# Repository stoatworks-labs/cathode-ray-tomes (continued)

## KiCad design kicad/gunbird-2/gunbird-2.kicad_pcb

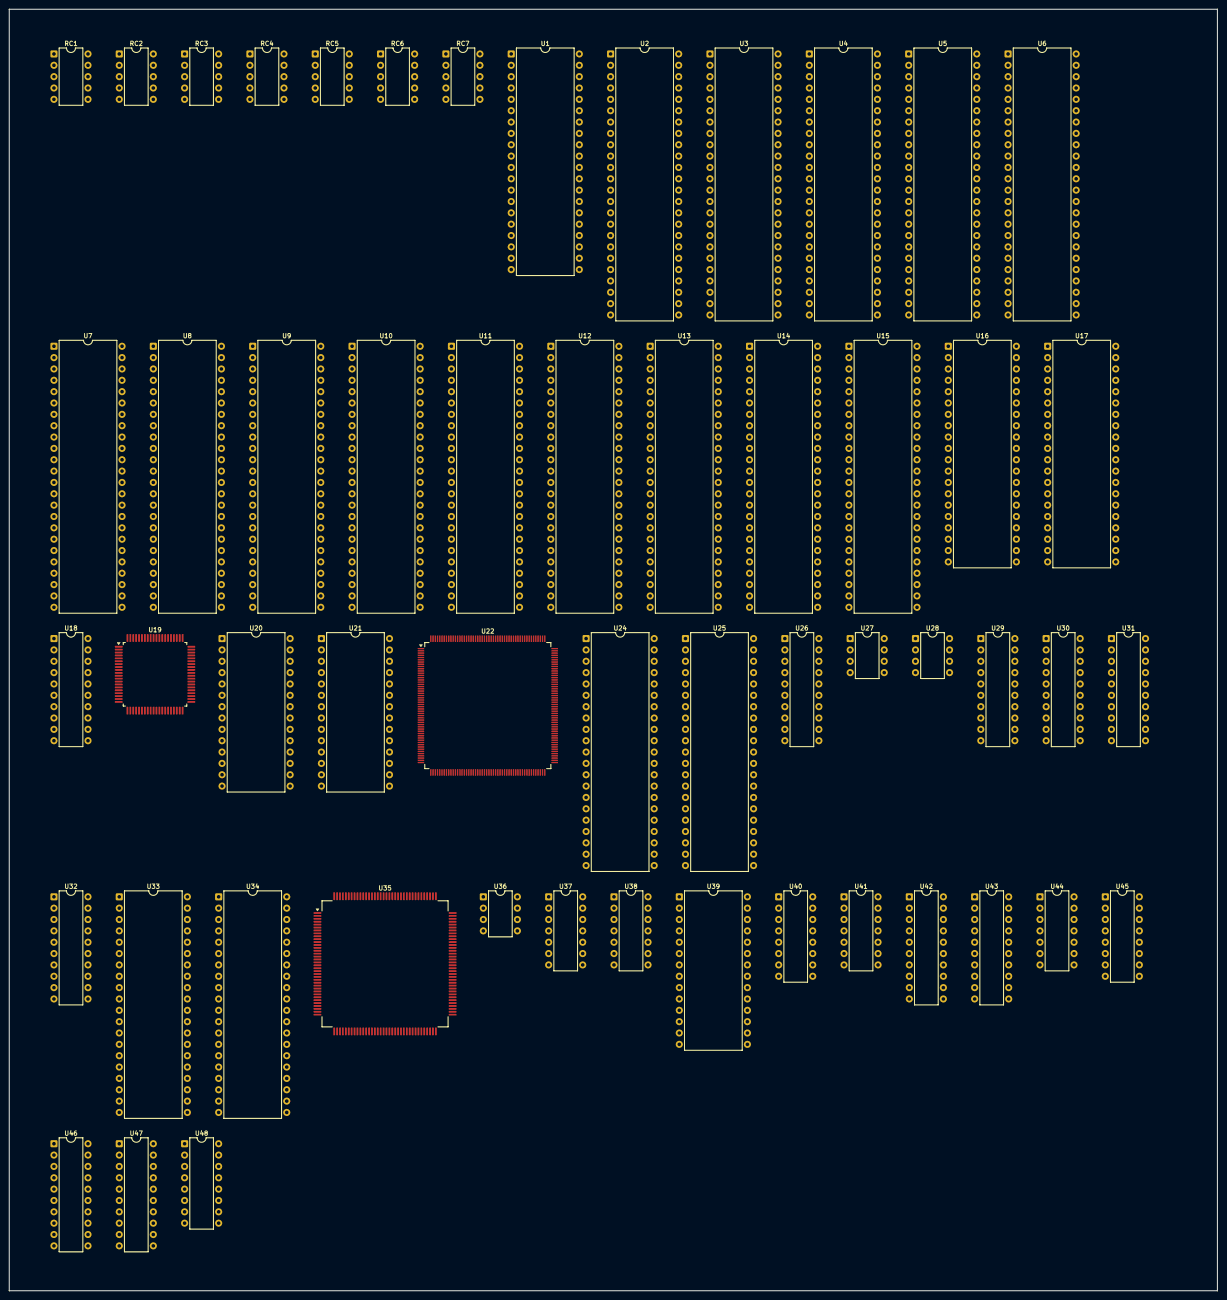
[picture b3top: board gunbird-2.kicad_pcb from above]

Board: 2 copper layers, 270.4 x 286.8 mm, 54 parts (0 on the bottom side), 309 nets, no tracks yet.

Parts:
RC1, RC2, RC3, RC4, RC5, RC6, RC7: RCx9; DIP-10_W7.62mm
U1, U16, U17: M27C4002; DIP-40_W15.24mm
U2, U3, U4, U5, U6, U7, U8, U9, U10, U11, U12, U13, U14, U15: LHMN5KUG-9835-38; DIP-48_W15.24mm
U18: PALACE16V8H-25; DIP-20_W7.62mm
U19: YMF278B-F; PQFP-80_14x14mm_P0.65mm
U20, U21: GLT725608-12J3; DIP-28_W15.24mm
U22: PS6406B_9808OAFB; PQFP-208_28x28mm_P0.5mm
U24, U25: OKI-HM51161-60AJ; DIP-42_W15.24mm
U26: 74LS273; DIP-20_W7.62mm
U27: 93C56X; DIP-8_W7.62mm
U28: 93LC56; DIP-8_W7.62mm
U29, U30, U31, U32, U42, U43, U46, U47: 74LS244; DIP-20_W7.62mm
U33, U34: OKI-M514260C-60J; DIP-40_W15.24mm
U35: HD6417604F28_SH2; PQFP-144_28x28mm_P0.65mm
U36: MB3771; DIP-8_W7.62mm
U37: 74LS08; DIP-14_W7.62mm
U38: 74LS14; DIP-14_W7.62mm
U39: YAC516-M; DIP-28_W15.24mm
U40: 74LS138; DIP-16_W7.62mm
U41: 74LS32; DIP-14_W7.62mm
U44: 4741-JCR; DIP-14_W7.62mm
U45: YAC513-M; DIP-16_W7.62mm
U48: HA13118; DIP-16_W7.62mm

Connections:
/2P_RIGHT: RC5.4, RC6.2
/CPU-~RD: U1.20, U2.14, U16.20, U17.20, U19.5, U22.33, U35.87, U41.12
/CPU_A0: U19.1, U35.30, U40.1
/MA0: U9.31, U19.52
/MA1: U9.11, U19.54
/MA2: U9.10, U19.57
/MA3: U9.9, U19.59
/MA4: U9.8, U19.61
/MA5: U9.7, U19.63
/MA6: U9.6, U19.67
/MA7: U9.5, U19.69
/MA8: U9.4, U19.70
/MA9: U9.42, U19.68
/MA10: U9.41, U19.64
/MA11: U9.40, U19.62
/MA12: U9.39, U19.60
/MA13: U9.38, U19.58
/MA14: U9.37, U19.56
/MA15: U9.36, U19.53
/MA16: U9.35, U19.51
/MA17: U9.34, U19.71
/MA18: U9.3, U19.73
/MA19: U9.2, U19.74
/MA20: U9.43, U19.75
/MAIN_A1: U1.21, U2.11, U19.2, U22.52, U35.31, U40.2
/MAIN_A2: U1.22, U2.10, U16.21, U17.21, U19.3, U22.51, U35.32, U40.3
/MAIN_A3: U1.23, U2.9, U16.22, U17.22, U22.50, U35.34
/MAIN_A4: U1.24, U2.8, U16.23, U17.23, U22.49, U35.35
/MAIN_A5: U1.25, U2.7, U16.24, U17.24, U22.48, U35.36
/MAIN_A6: U1.26, U2.6, U16.25, U17.25, U22.47, U35.37
/MAIN_A7: U1.27, U2.5, U16.26, U17.26, U22.46, U35.38
/MAIN_A8: U1.28, U2.4, U16.27, U17.27, U22.45, U35.39
/MAIN_A9: U1.29, U2.42, U16.28, U17.28, U22.44, U35.41
/MAIN_A10: U1.31, U2.41, U16.29, U17.29, U22.43, U35.43
/MAIN_A11: U1.32, U2.40, U16.31, U17.31, U22.41, U35.44
/MAIN_A12: U1.33, U2.39, U16.32, U17.32, U22.40, U35.45
/MAIN_A13: U1.34, U2.38, U16.33, U17.33, U22.39, U35.46
/MAIN_A14: U1.35, U2.37, U16.34, U17.34, U22.38, U35.47
/MAIN_A15: U1.36, U2.36, U16.35, U17.35, U22.37, U35.49
/MAIN_A16: U1.37, U2.35, U16.36, U17.36, U22.36, U35.51
/MAIN_A17: U1.38, U2.34, U16.37, U17.37, U22.35, U35.52
/MAIN_A18: U1.39, U2.3, U16.38, U17.38, U22.34, U35.53
/MAIN_A19: U2.2, U16.39, U35.55
/MAIN_A20: U2.43, U18.1, U35.57
/MAIN_A21: U2.44, U18.2, U35.58
/MAIN_A22: U2.1, U18.3, U35.59
/MAIN_A23: U18.4, U35.61
/MAIN_A24: U18.5, U35.63
/MAIN_D0: U1.19, U2.15, U16.19, U19.10, U22.20, U24.2, U26.3, U29.18, U33.2, U35.130, U42.18, U43.18, U46.18, U47.18
/MAIN_D1: U1.18, U2.17, U16.18, U19.11, U22.19, U24.3, U26.4, U29.16, U33.3, U35.131, U42.16, U43.16, U46.16, U47.16
/MAIN_D2: U1.17, U2.19, U16.17, U19.12, U22.18, U24.4, U26.7, U29.14, U33.4, U35.133, U42.14, U43.14, U46.14, U47.14
/MAIN_D3: U1.16, U2.21, U16.16, U19.13, U22.17, U24.5, U26.8, U29.12, U33.5, U35.135, U42.12, U43.12, U46.12, U47.12
/MAIN_D4: U1.15, U2.24, U16.15, U19.14, U22.15, U24.7, U26.13, U29.9, U33.7, U35.136, U42.9, U43.9, U46.9, U47.9
/MAIN_D5: U1.14, U2.26, U16.14, U19.15, U22.14, U24.8, U26.14, U29.7, U33.8, U35.137, U42.7, U43.7, U46.7, U47.7
/MAIN_D6: U1.13, U2.28, U16.13, U19.16, U22.12, U24.9, U26.17, U29.5, U33.9, U35.138, U42.5, U43.5, U46.5, U47.5
/MAIN_D7: U1.12, U2.30, U16.12, U19.17, U22.11, U24.10, U26.18, U29.3, U33.10, U35.140, U42.3, U43.3, U46.3, U47.3
/MAIN_D8: U1.10, U2.16, U16.10, U22.10, U24.33, U33.31, U35.142
/MAIN_D9: U1.9, U2.18, U16.9, U22.9, U24.34, U33.32, U35.143
/MAIN_D10: U1.8, U2.20, U16.8, U22.8, U24.35, U33.33, U35.144
/MAIN_D11: U1.7, U2.22, U16.7, U22.7, U24.36, U33.34, U35.1
/MAIN_D12: U1.6, U2.25, U16.6, U22.5, U24.38, U33.36, U35.2
/MAIN_D13: U1.5, U2.27, U16.5, U22.4, U24.39, U33.37, U35.3
/MAIN_D14: U1.4, U2.29, U16.4, U22.3, U24.40, U33.38, U35.5
/MAIN_D15: U1.3, U2.31, U16.3, U22.2, U24.41, U33.39, U35.7
/MAIN_D16: U17.19, U25.2, U34.2, U35.8
/MAIN_D17: U17.18, U25.3, U34.3, U35.9
/MAIN_D18: U17.17, U25.4, U34.4, U35.10
/MAIN_D19: U17.16, U25.5, U34.5, U35.11
/MAIN_D20: U17.15, U25.7, U34.7, U35.13
/MAIN_D21: U17.14, U25.8, U34.8, U35.15
/MAIN_D22: U17.13, U25.9, U34.9, U35.16
/MAIN_D23: U17.12, U25.10, U34.10, U35.17
/MAIN_D24: U17.10, U25.33, U34.31, U35.19
/MAIN_D25: U17.9, U25.34, U34.32, U35.21
/MAIN_D26: U17.8, U25.35, U34.33, U35.22
/MAIN_D27: U17.7, U25.36, U34.34, U35.23
/MAIN_D28: U17.6, U25.38, U34.36, U35.25
/MAIN_D29: U17.5, U25.39, U34.37, U35.27
/MAIN_D30: U17.4, U25.40, U34.38, U35.28
/MAIN_D31: U17.3, U25.41, U34.39, U35.29
/MD0: U9.15, U19.49
/MD1: U9.17, U19.47
/MD2: U9.19, U19.44
/MD3: U9.21, U19.42
/MD4: U9.24, U19.41
/MD5: U9.26, U19.43
/MD6: U9.28, U19.46
/MD7: U9.30, U19.48
/PAL2: U18.14, U22.30
/XI_VC: U22.25, U37.13
/main/FTI: U18.19, U35.99
/main/MD3: U18.18, U35.117
/main/MD4: U18.17, U35.119
/main/MD5: U35.120, U38.1
/main/memories/AD_O4: U40.11, U41.10, U41.13
/main/memories/AR2: U24.17, U25.17, U33.16, U34.16
/main/memories/AR3: U24.18, U25.18, U33.17, U34.17
/main/memories/AR4: U24.19, U25.19, U33.18, U34.18
/main/memories/AR5: U24.20, U25.20, U33.19, U34.19
/main/memories/AR6: U24.23, U25.23, U33.22, U34.22
/main/memories/AR7: U24.24, U25.24, U33.23, U34.23
/main/memories/AR8: U24.25, U25.25, U33.24, U34.24
/main/memories/AR9: U24.26, U25.26, U33.25, U34.25
/main/memories/AR10: U24.27, U25.27, U33.26, U34.26
/main/memories/AR11: U24.28, U25.28
/main/memories/AR12: U24.16, U25.16
/main/memories/AR13: U24.15, U25.15
/main/memories/CLK_AD: U26.11, U41.8
/main/memories/ORG: U26.2, U27.8, U28.6
/main/memories/PAL_4: U18.16, U40.4
/main/memories/Q5: U26.15, U27.5, U28.3, U29.13
/main/memories/Q6: U26.16, U27.4, U28.2, U29.15
/main/memories/Q7: U26.19, U27.3, U28.1, U29.17
/main/memories/~EE: U1.2, U2.12, U18.13
/main/memories/~E: U16.2, U17.2, U18.12
/main/~1P_RD: U40.15, U42.1, U42.19
/main/~2P_RD: U40.14, U43.1, U43.19
/main/~CAB_RD: U40.12, U46.1, U46.19
/main/~CONN7_RD: U40.13, U47.1, U47.19
/main/~CS0: U18.6, U35.72
/main/~CS1: U18.7, U35.73
/main/~CS2: U18.8, U35.74
/main/~RAS: U24.14, U25.14, U33.14, U34.14
/main/~RESET_CPU: U35.122, U37.3
/main/~WR: U18.9, U24.13, U25.13, U33.13, U34.13
/objects/BLUE0: U22.54, U30.2
/objects/BLUE1: U22.55, U30.4
/objects/BLUE2: U22.56, U30.6
/objects/BLUE3: U22.57, U30.8
/objects/BLUE4: U22.58, U30.11
/objects/BLUE5: U22.59, U30.13
/objects/BLUE6: U22.60, U30.15
/objects/BLUE7: U22.61, U30.17
/objects/D0: U10.15, U11.15, U12.15, U13.15, U14.15, U15.15, U22.189
/objects/D1: U10.17, U11.17, U12.17, U13.17, U14.17, U15.17, U22.188
/objects/D2: U10.19, U11.19, U12.19, U13.19, U14.19, U15.19, U22.187
/objects/D3: U10.21, U11.21, U12.21, U13.21, U14.21, U15.21, U22.186
/objects/D4: U10.24, U11.24, U12.24, U13.24, U14.24, U15.24, U22.184
/objects/D5: U10.26, U11.26, U12.26, U13.26, U14.26, U15.26, U22.183
/objects/D6: U10.28, U11.28, U12.28, U13.28, U14.28, U15.28, U22.182
/objects/D7: U10.30, U11.30, U12.30, U13.30, U14.30, U15.30, U22.181
/objects/D8: U10.16, U11.16, U12.16, U13.16, U14.16, U15.16, U22.180
/objects/D9: U10.18, U11.18, U12.18, U13.18, U14.18, U15.18, U22.179
/objects/D10: U10.20, U11.20, U12.20, U13.20, U14.20, U15.20, U22.178
/objects/D11: U10.22, U11.22, U12.22, U13.22, U14.22, U15.22, U22.177
/objects/D12: U10.25, U11.25, U12.25, U13.25, U14.25, U15.25, U22.176
/objects/D13: U10.27, U11.27, U12.27, U13.27, U14.27, U15.27, U22.175
/objects/D14: U10.29, U11.29, U12.29, U13.29, U14.29, U15.29, U22.174
/objects/D15: U10.31, U11.31, U12.31, U13.31, U14.31, U15.31, U22.173
/objects/D16: U3.15, U4.15, U5.15, U6.15, U7.15, U8.15, U22.207
/objects/D17: U3.17, U4.17, U5.17, U6.17, U7.17, U8.17, U22.206
/objects/D18: U3.19, U4.19, U5.19, U6.19, U7.19, U8.19, U22.205
/objects/D19: U3.21, U4.21, U5.21, U6.21, U7.21, U8.21, U22.204
/objects/D20: U3.24, U4.24, U5.24, U6.24, U7.24, U8.24, U22.203
/objects/D21: U3.26, U4.26, U5.26, U6.26, U7.26, U8.26, U22.202
/objects/D22: U3.28, U4.28, U5.28, U6.28, U7.28, U8.28, U22.201
/objects/D23: U3.30, U4.30, U5.30, U6.30, U7.30, U8.30, U22.200
/objects/D24: U3.16, U4.16, U5.16, U6.16, U7.16, U8.16, U22.198
/objects/D25: U3.18, U4.18, U5.18, U6.18, U7.18, U8.18, U22.197
/objects/D26: U3.20, U4.20, U5.20, U6.20, U7.20, U8.20, U22.196
/objects/D27: U3.22, U4.22, U5.22, U6.22, U7.22, U8.22, U22.195
/objects/D28: U3.25, U4.25, U5.25, U6.25, U7.25, U8.25, U22.194
/objects/D29: U3.27, U4.27, U5.27, U6.27, U7.27, U8.27, U22.193
/objects/D30: U3.29, U4.29, U5.29, U6.29, U7.29, U8.29, U22.192
/objects/D31: U3.31, U4.31, U5.31, U6.31, U7.31, U8.31, U22.191
/objects/GREEN0: U22.62, U31.2
/objects/GREEN1: U22.63, U31.4
/objects/GREEN2: U22.64, U31.6
/objects/GREEN3: U22.66, U31.8
/objects/GREEN4: U22.67, U31.11
/objects/GREEN5: U22.68, U31.13
/objects/GREEN6: U22.69, U31.15
/objects/GREEN7: U22.70, U31.17
/objects/RAMA0: U20.10, U21.10, U22.110
/objects/RAMA1: U20.9, U21.9, U22.109
/objects/RAMA2: U20.8, U21.8, U22.108
/objects/RAMA3: U20.7, U21.7, U22.107
/objects/RAMA4: U20.6, U21.6, U22.106
/objects/RAMA5: U20.5, U21.5, U22.105
/objects/RAMA6: U20.4, U21.4, U22.103
/objects/RAMA7: U20.3, U21.3, U22.102
/objects/RAMA8: U20.25, U21.25, U22.101
/objects/RAMA9: U20.24, U21.24, U22.100
/objects/RAMA10: U20.21, U21.21, U22.98
/objects/RAMA11: U20.23, U21.23, U22.97
/objects/RAMA12: U20.2, U21.2, U22.95
/objects/RAMA13: U20.26, U21.26, U22.94
/objects/RAMA14: U20.1, U21.1, U22.93
/objects/RAMD0: U21.11, U22.133
/objects/RAMD1: U21.12, U22.132
/objects/RAMD2: U21.13, U22.131
/objects/RAMD3: U21.15, U22.130
/objects/RAMD4: U21.16, U22.129
/objects/RAMD5: U21.17, U22.128
/objects/RAMD6: U21.18, U22.127
/objects/RAMD7: U21.19, U22.126
/objects/RAMD8: U20.11, U22.125
/objects/RAMD9: U20.12, U22.124
/objects/RAMD10: U20.13, U22.123
/objects/RAMD11: U20.15, U22.122
/objects/RAMD12: U20.16, U22.120
/objects/RAMD13: U20.17, U22.119
/objects/RAMD14: U20.18, U22.118
/objects/RAMD15: U20.19, U22.117
/objects/RED0: U22.71, U32.2
/objects/RED1: U22.72, U32.4
/objects/RED2: U22.73, U32.6
/objects/RED3: U22.74, U32.8
/objects/RED4: U22.75, U32.11
/objects/RED5: U22.76, U32.13
/objects/RED6: U22.77, U32.15
/objects/RED7: U22.78, U32.17
/objects/VC0: U3.11, U4.11, U5.11, U6.11, U7.11, U8.11, U10.11, U11.11, U12.11, U13.11, U14.11, U15.11, U22.171
/objects/VC1: U3.10, U4.10, U5.10, U6.10, U7.10, U8.10, U10.10, U11.10, U12.10, U13.10, U14.10, U15.10, U22.170
/objects/VC2: U3.9, U4.9, U5.9, U6.9, U7.9, U8.9, U10.9, U11.9, U12.9, U13.9, U14.9, U15.9, U22.169
/objects/VC3: U3.8, U4.8, U5.8, U6.8, U7.8, U8.8, U10.8, U11.8, U12.8, U13.8, U14.8, U15.8, U22.168
/objects/VC4: U3.7, U4.7, U5.7, U6.7, U7.7, U8.7, U10.7, U11.7, U12.7, U13.7, U14.7, U15.7, U22.166
/objects/VC5: U3.6, U4.6, U5.6, U6.6, U7.6, U8.6, U10.6, U11.6, U12.6, U13.6, U14.6, U15.6, U22.165
/objects/VC6: U3.5, U4.5, U5.5, U6.5, U7.5, U8.5, U10.5, U11.5, U12.5, U13.5, U14.5, U15.5, U22.163
/objects/VC7: U3.4, U4.4, U5.4, U6.4, U7.4, U8.4, U10.4, U11.4, U12.4, U13.4, U14.4, U15.4, U22.162
/objects/VC8: U3.42, U4.42, U5.42, U6.42, U7.42, U8.42, U10.42, U11.42, U12.42, U13.42, U14.42, U15.42, U22.161
/objects/VC9: U3.41, U4.41, U5.41, U6.41, U7.41, U8.41, U10.41, U11.41, U12.41, U13.41, U14.41, U15.41, U22.160
/objects/VC10: U3.40, U4.40, U5.40, U6.40, U7.40, U8.40, U10.40, U11.40, U12.40, U13.40, U14.40, U15.40, U22.159
/objects/VC11: U3.39, U4.39, U5.39, U6.39, U7.39, U8.39, U10.39, U11.39, U12.39, U13.39, U14.39, U15.39, U22.158
/objects/VC12: U3.38, U4.38, U5.38, U6.38, U7.38, U8.38, U10.38, U11.38, U12.38, U13.38, U14.38, U15.38, U22.156
/objects/VC13: U3.37, U4.37, U5.37, U6.37, U7.37, U8.37, U10.37, U11.37, U12.37, U13.37, U14.37, U15.37, U22.155
/objects/VC14: U3.36, U4.36, U5.36, U6.36, U7.36, U8.36, U10.36, U11.36, U12.36, U13.36, U14.36, U15.36, U22.154
/objects/VC15: U3.35, U4.35, U5.35, U6.35, U7.35, U8.35, U10.35, U11.35, U12.35, U13.35, U14.35, U15.35, U22.153
/objects/VC16: U3.34, U4.34, U5.34, U6.34, U7.34, U8.34, U10.34, U11.34, U12.34, U13.34, U14.34, U15.34, U22.151
/objects/VC17: U3.3, U4.3, U5.3, U6.3, U7.3, U8.3, U10.3, U11.3, U12.3, U13.3, U14.3, U15.3, U22.150
/objects/VC18: U3.2, U4.2, U5.2, U6.2, U7.2, U8.2, U10.2, U11.2, U12.2, U13.2, U14.2, U15.2, U22.148
/objects/VC19: U3.43, U4.43, U5.43, U6.43, U7.43, U8.43, U10.43, U11.43, U12.43, U13.43, U14.43, U15.43, U22.147
/objects/VC20: U3.44, U4.44, U5.44, U6.44, U7.44, U8.44, U10.44, U11.44, U12.44, U13.44, U14.44, U15.44, U22.146
/objects/VC21: U3.1, U4.1, U5.1, U6.1, U7.1, U8.1, U10.1, U11.1, U12.1, U13.1, U14.1, U15.1, U22.145
/objects/memories_vc/~CS2: U4.12, U11.12
/objects/memories_vc/~CS3: U5.12, U12.12
/objects/memories_vc/~CS4: U6.12, U13.12
/objects/memories_vc/~CS5: U7.12, U14.12
/objects/memories_vc/~CS6: U8.12, U15.12
/objects/~BRIGHT: U22.88, U38.9
/objects/~CE: U20.20, U21.20, U22.113
/objects/~OE_RAM: U20.22, U21.22, U22.112
/objects/~OE_ROM: U3.14, U4.14, U5.14, U6.14, U7.14, U8.14, U10.14, U11.14, U12.14, U13.14, U14.14, U15.14, U22.135
/objects/~SYNC: U22.87, U38.3
/objects/~WEH: U21.27, U22.116
/objects/~WEL: U20.27, U22.115
/sound/BCO: U19.20, U39.8, U45.5
/sound/CLKOUT: U19.19, U39.6
/sound/DO2: U19.24, U39.9, U45.8
/sound/INPUT_A: U39.20, U44.3
/sound/LRO: U19.21, U39.10, U45.7
/sound/MP: U44.8, U44.9, U45.14
/sound/SWIN: U44.13, U44.14, U45.13
/sound/WCO: U19.45, U45.6
/sound/~MCS0: U9.44, U19.25
/sound/~MRD: U9.14, U19.50
/~CS[1..6]: U3.12, U10.12
/~FM_IRQ: U19.9, U35.126, U37.4
/~IRL_VC: U22.28, U37.5
/~MR: U26.1, U36.8, U37.2
/~SND_CS: U18.15, U19.4
/~SND_IC: U19.7, U26.5, U39.4, U39.5
/~WAIT: U22.27, U35.89
/~WE0: U19.6, U22.32, U25.31, U34.29
/~WE1: U22.31, U25.30, U34.28
/~WE2: U24.31, U33.29
/~WE3: U24.30, U33.28
unnamed: U22.80, U22.81
unnamed: RC1.3, U46.11
unnamed: RC1.5, U46.13
unnamed: RC1.7, U46.15
unnamed: RC1.9, U46.17
unnamed: RC2.3, U42.11
unnamed: RC2.5, U42.13
unnamed: RC2.7, U42.15
unnamed: RC2.9, U42.17
unnamed: RC3.3, U42.8
unnamed: RC3.5, U42.6
unnamed: RC3.7, U42.4
unnamed: RC3.9, U42.2
unnamed: RC4.3, U47.11
unnamed: RC4.5, U47.13
unnamed: RC4.7, U47.15
unnamed: RC4.9, U47.17
unnamed: RC5.3, U43.11
unnamed: RC5.5, U43.13
unnamed: RC5.7, U43.15
unnamed: RC5.9, U43.17
unnamed: RC6.3, U43.8
unnamed: RC6.5, U43.6
unnamed: RC6.7, U43.4
unnamed: RC6.9, U43.2
unnamed: RC7.3, U47.8
unnamed: RC7.5, U47.6
unnamed: RC7.7, U47.4
unnamed: RC7.9, U47.2
unnamed: U28.4, U29.11
unnamed: U29.1, U29.19, U41.11
unnamed: U35.127, U37.6
unnamed: U37.1, U38.2
unnamed: U39.22, U39.26
unnamed: U44.1, U44.2
unnamed: U44.6, U44.7
unnamed: U44.10, U45.15
unnamed: U44.12, U45.16
unnamed: U38.13, U46.2
unnamed: U38.11, U46.4
VCC: RC1.1, RC2.1, RC3.1, RC4.1, RC5.1, RC6.1, RC7.1, U1.1, U1.40, U2.23, U2.33, U3.23, U3.33, U4.23, U4.33, U5.23, U5.33, U6.23, U6.33, U7.23, U7.33, U8.23, U8.33, U9.23, U10.23, U10.33, U11.23, U11.33, U12.23, U12.33, U13.23, U13.33, U14.23, U14.33, U15.23, U15.33, U16.1, U16.40, U17.1, U17.40, U18.11, U18.20, U19.8, U19.32, U19.55, U19.72, U20.28, U21.28, U22.1, U22.16, U22.24, U22.53, U22.99, U22.114, U22.137, U22.152, U22.167, U22.190, U24.1, U24.6, U24.21, U25.1, U25.6, U25.21, U27.2, U28.8, U29.20, U30.20, U31.20, U32.20, U33.1, U33.6, U33.20, U34.1, U34.6, U34.20, U35.4, U35.12, U35.18, U35.24, U35.40, U35.48, U35.54, U35.60, U35.67, U35.84, U35.92, U35.96, U35.104, U35.110, U35.112, U35.113, U35.123, U35.125, U35.128, U35.129, U35.132, U35.139, U36.5, U36.6, U37.12, U37.14, U38.14, U39.2, U39.7, U40.6, U42.20, U43.20, U44.4, U45.1, U45.3, U46.20, U47.20, U48.13
VSS: RC1.10, RC2.10, RC3.10, RC5.10, RC6.10, RC7.10, U1.11, U1.30, U2.13, U2.32, U3.13, U3.32, U4.13, U4.32, U5.13, U5.32, U6.13, U6.32, U7.13, U7.32, U8.13, U8.32, U9.1, U9.12, U9.13, U9.32, U9.33, U10.13, U10.32, U11.13, U11.32, U12.13, U12.32, U13.13, U13.32, U14.13, U14.32, U15.13, U15.32, U16.11, U16.30, U17.11, U17.30, U18.10, U19.18, U19.37, U19.65, U19.78, U20.14, U21.14, U22.13, U22.21, U22.29, U22.42, U22.65, U22.79, U22.90, U22.96, U22.104, U22.121, U22.134, U22.142, U22.149, U22.157, U22.164, U22.172, U22.185, U22.199, U22.208, U24.22, U24.29, U24.37, U24.42, U25.22, U25.29, U25.37, U25.42, U27.7, U28.5, U29.2, U29.4, U29.6, U29.8, U29.10, U30.1, U30.10, U30.19, U31.1, U31.10, U31.19, U32.1, U32.10, U32.19, U33.21, U33.27, U33.35, U33.40, U34.21, U34.27, U34.35, U34.40, U35.6, U35.14, U35.20, U35.26, U35.33, U35.42, U35.50, U35.56, U35.62, U35.69, U35.70, U35.71, U35.78, U35.86, U35.91, U35.98, U35.105, U35.106, U35.115, U35.121, U35.134, U35.141, U36.2, U36.4, U37.7, U38.7, U39.1, U39.3, U39.23, U39.27, U40.5, U42.10, U43.10, U44.11, U45.2, U45.4, U45.9, U45.12, U46.6, U46.8, U46.10, U47.10, U48.4, U48.12

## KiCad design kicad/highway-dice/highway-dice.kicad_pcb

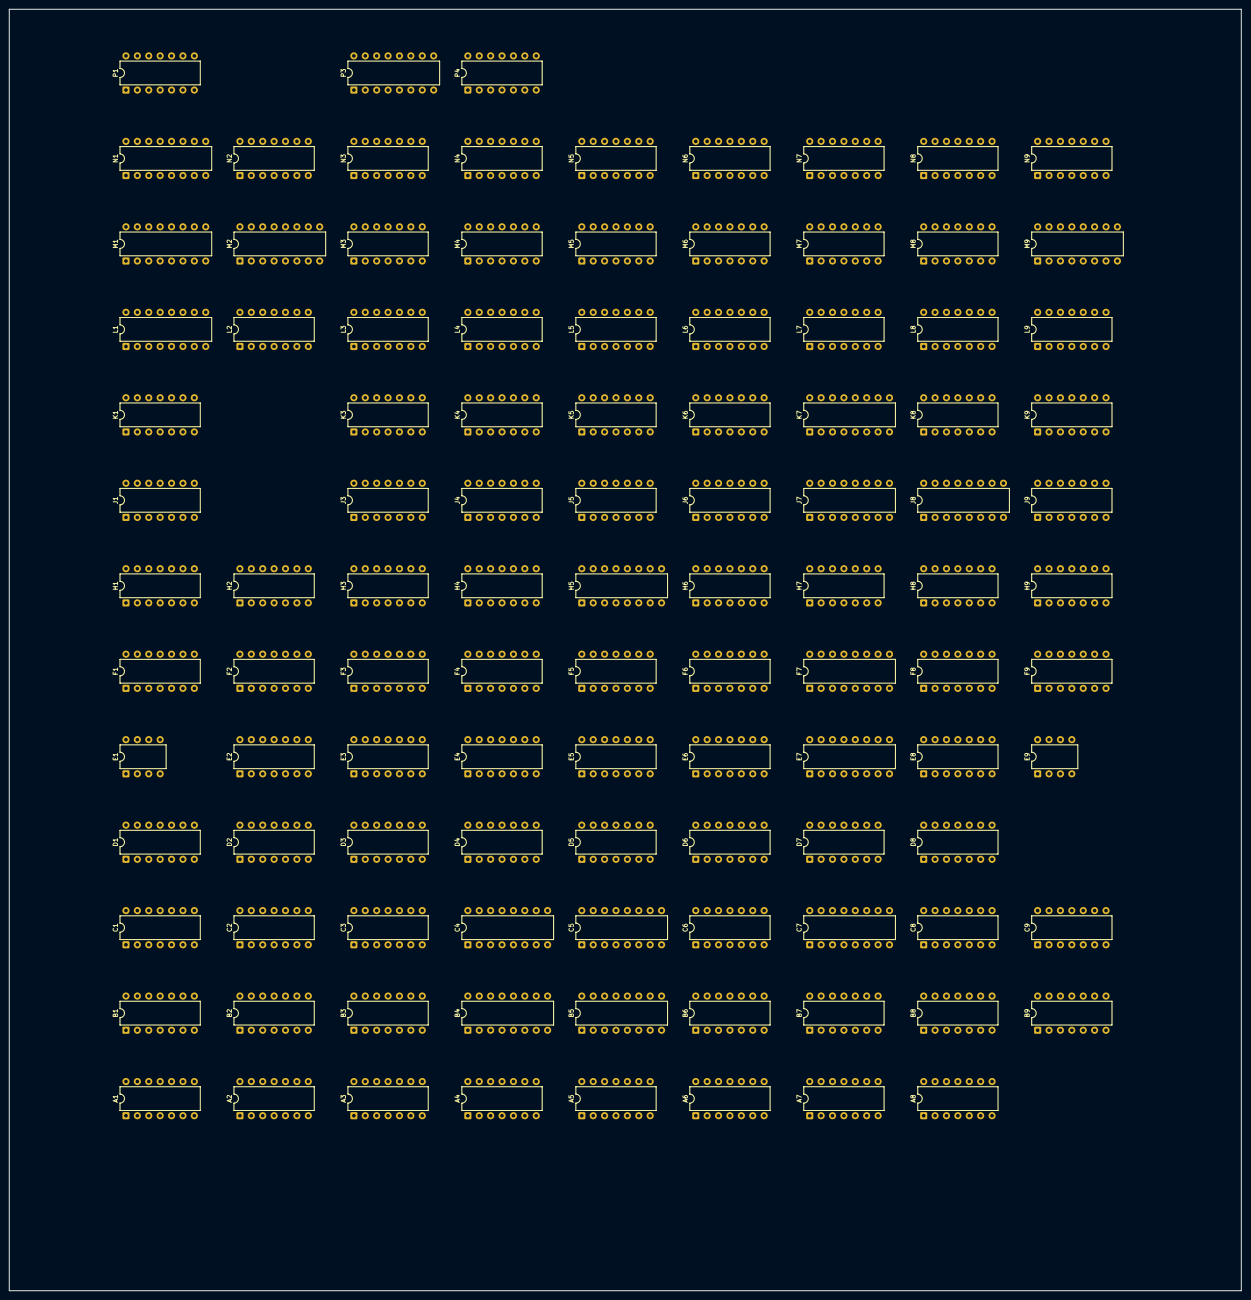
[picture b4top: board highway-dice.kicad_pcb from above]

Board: 2 copper layers, 274.6 x 285.6 mm, 107 parts (0 on the bottom side), 377 nets, no tracks yet.

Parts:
A1, A4: 7400; DIP-14_W7.62mm
A2: 7404; DIP-14_W7.62mm
A3: 7405; DIP-14_W7.62mm
A5: 7427; DIP-14_W7.62mm
A6: 7410; DIP-14_W7.62mm
A7, A8: 7493; DIP-14_W7.62mm
B1, B6: 7420; DIP-14_W7.62mm
B2: 7493; DIP-14_W7.62mm
B3: 7486; DIP-14_W7.62mm
B4, B5: 74193; DIP-16_W7.62mm
B7: 7402; DIP-14_W7.62mm
B8: 7400; DIP-14_W7.62mm
B9: 7406; DIP-14_W7.62mm
C1: 74107; DIP-14_W7.62mm
C2, C6: 7493; DIP-14_W7.62mm
C3: 7486; DIP-14_W7.62mm
C4, C5: 74193; DIP-16_W7.62mm
C7: 74145; DIP-16_W7.62mm
C8: 7474; DIP-14_W7.62mm
C9: 7492; DIP-14_W7.62mm
D1: 7402; DIP-14_W7.62mm
D2, D7: 7404; DIP-14_W7.62mm
D3: 7405; DIP-14_W7.62mm
D4, D6: 7400; DIP-14_W7.62mm
D5: 7410; DIP-14_W7.62mm
D8: 7420; DIP-14_W7.62mm
E1: 2533; DIP-8_W7.62mm
E2: 7410; DIP-14_W7.62mm
E3, E5: 7404; DIP-14_W7.62mm
E4: 7474; DIP-14_W7.62mm
E6: 7486; DIP-14_W7.62mm
E7: 74193; DIP-16_W7.62mm
E8: 7493; DIP-14_W7.62mm
E9: 555; DIP-8_W7.62mm
F1: 7402; DIP-14_W7.62mm
F2: 7486; DIP-14_W7.62mm
F3: 7493; DIP-14_W7.62mm
F4, F6, F8: 7400; DIP-14_W7.62mm
F5: 74164; DIP-14_W7.62mm
F7: 74279; DIP-16_W7.62mm
F9: 74132; DIP-14_W7.62mm
H1: 7420; DIP-14_W7.62mm
H2: 7430; DIP-14_W7.62mm
H3: 7493; DIP-14_W7.62mm
H4: 7410; DIP-14_W7.62mm
H5: 74165; DIP-16_W7.62mm
H6, H9: 7474; DIP-14_W7.62mm
H7: 7402; DIP-14_W7.62mm
H8: 7404; DIP-14_W7.62mm
J1: 7474; DIP-14_W7.62mm
J3, J6: 7404; DIP-14_W7.62mm
J4: 7493; DIP-14_W7.62mm
J5: 7486; DIP-14_W7.62mm
J7: 9316; DIP-16_W7.62mm
J8: 74193; DIP-16_W7.62mm
J9: 7405; DIP-14_W7.62mm
K1, K5: 7420; DIP-14_W7.62mm
K3, K4: 7493; DIP-14_W7.62mm
K6, K9: 7400; DIP-14_W7.62mm
K7: 9316; DIP-16_W7.62mm
K8: 7486; DIP-14_W7.62mm
L1: 9312; DIP-16_W7.62mm
L2: 7493; DIP-14_W7.62mm
L3, L8: 7400; DIP-14_W7.62mm
L4: 7420; DIP-14_W7.62mm
L5, L9: 7404; DIP-14_W7.62mm
L6: 74107; DIP-14_W7.62mm
L7: 7410; DIP-14_W7.62mm
M1: 7448; DIP-16_W7.62mm
M2: 9322; DIP-16_W7.62mm
M3, M4, M7: 7493; DIP-14_W7.62mm
M5: 7420; DIP-14_W7.62mm
M6: 7486; DIP-14_W7.62mm
M8: 74107; DIP-14_W7.62mm
M9: 74145; DIP-16_W7.62mm
N1: 9312; DIP-16_W7.62mm
N2: 7490; DIP-14_W7.62mm
N3, N5: 7410; DIP-14_W7.62mm
N4: 7400; DIP-14_W7.62mm
N6: 7408; DIP-14_W7.62mm
N7, N9: 7493; DIP-14_W7.62mm
N8: 74107; DIP-14_W7.62mm
P1: 7427; DIP-14_W7.62mm
P3: 74279; DIP-16_W7.62mm
P4: 7404; DIP-14_W7.62mm

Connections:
+5V: A1.14, A2.14, A3.14, A4.14, A5.14, A6.14, A7.5, A8.5, B1.14, B2.5, B3.14, B4.16, B5.16, B6.14, B7.14, B8.14, B9.14, C1.14, C2.5, C3.14, C4.16, C5.16, C6.5, C7.16, C8.14, C9.5, D1.14, D2.14, D3.14, D4.14, D5.14, D6.14, D7.14, D8.14, E2.14, E3.14, E4.14, E5.14, E6.14, E7.16, E8.5, E9.8, F1.14, F2.14, F3.5, F4.14, F5.14, F6.14, F7.16, F8.14, F9.14, H1.14, H2.14, H3.5, H4.14, H5.16, H6.14, H7.14, H8.14, H9.14, J1.14, J3.14, J4.5, J5.14, J6.14, J7.16, J8.16, J9.14, K1.14, K3.5, K4.5, K5.14, K6.14, K7.16, K8.14, K9.14, L1.16, L2.5, L3.14, L4.14, L5.14, L6.14, L7.14, L8.14, L9.14, M1.16, M2.16, M3.5, M4.5, M5.14, M6.14, M7.5, M8.14, M9.16, N1.16, N2.5, N3.14, N4.14, N5.14, N6.14, N7.5, N8.14, N9.5, P1.14, P3.16, P4.14
A1-3: A1.3, B1.4, E4.11
A1-4: A1.4, C1.5
A1-8: A1.8, E2.5, E2.9
A1-9: A1.9, A4.10, F2.9, J1.9
A1-10: A1.10, F2.5, J1.5
A1-11: A1.11, F1.8
A1-12: A1.12, A2.10, B1.2
A2-11: A2.11, B1.8, E1.6
A3-1: A3.1, B3.3
A3-3: A3.3, B3.11
A3-5: A3.5, B3.6
A3-9: A3.9, B3.8
A4-1: A4.1, A4.13, A5.8, A6.2, K6.1
A4-3: A4.3, A4.4
A4-6: A4.6, N9.1
A4-8: A4.8, H6.13
A4-9: A4.9, J1.2, J1.6, J1.11
A5-3: A5.3, B4.1, B5.2, B6.9
A5-4: A5.4, B4.10, B5.6, B6.10
A5-5: A5.5, B4.9, B5.7, B6.12
A5-6: A5.6, B8.13
A5-12: A5.12, A6.10, D5.10
A6-3: A6.3, B8.11, C8.13
A6-4: A6.4, B8.10, C8.6
A6-5: A6.5, B6.8, C8.10
A6-6: A6.6, A6.9
A6-8: A6.8, E5.13
A6-12: A6.12, F7.5, F7.10
A7-1: A7.1, A7.12
A7-11: A7.11, N2.14
A7-14: A7.14, A8.11
A8-1: A8.1, A8.12
B1-5: B1.5, E1.1, E1.7, E4.12
B1-6: B1.6, P1.9
B1-10: B1.10, D2.3, E2.8
B3-1: B3.1, B4.2
B3-4: B3.4, B4.3
B3-10: B3.10, B4.6
B3-13: B3.13, B4.7
B4-4: B4.4, C4.13
B4-5: B4.5, C4.12
B4-15: B4.15, B5.3
B5-4: B5.4, C5.13
B5-5: B5.5, C5.12
B5-11: B5.11, B5.12, C5.11
B5-13: B5.13, E5.11
B5-14: B5.14, C5.14, E5.10
B6-1: B6.1, E5.12
B6-2: B6.2, C6.11, C7.13
B6-4: B6.4, C6.9, C7.15
B6-5: B6.5, C6.8, C7.14
B6-6: B6.6, B7.3, B7.6
B7-1: B7.1, D7.3
B7-2: B7.2, C8.9
B7-4: B7.4, D7.9
B7-5: B7.5, C8.8
B7-8: B7.8, K5.8
B7-10: B7.10, K5.1, N5.1
B8-2: B8.2, C8.5, C8.11
B8-3: B8.3, B8.4
B8-5: B8.5, B8.8
B8-6: B8.6, C8.3
C3-1: C3.1, C4.2
C3-3: C3.3, D3.13
C3-4: C3.4, C4.3
C3-5: C3.5, D3.4
C3-6: C3.6, D3.5
C3-8: C3.8, D3.9
C3-10: C3.10, C4.6
C3-11: C3.11, D3.11
C3-13: C3.13, C4.7
C4-1: C4.1, C5.2
C4-4: C4.4, D4.3
C4-5: C4.5, D4.6
C4-9: C4.9, C5.7
C4-10: C4.10, C5.6
C4-15: C4.15, C5.3
C5-4: C5.4, D4.11
C5-5: C5.5, D4.8
C7-2: C7.2, C7.4, C7.6, C7.9, D7.13
C7-3: C7.3, C7.7, D7.11
C7-5: C7.5, D7.5
C9-1: C9.1, J6.3, N8.9, N8.12, N9.14
D1-4: D1.4, H2.1
D1-8: D1.8, H2.8, N1.10
D1-10: D1.10, D2.5
D1-13: D1.13, K4.14
D2-1: D2.1, F1.6, H4.8
D2-6: D2.6, L1.10
D2-10: D2.10, M8.10
D3-2: D3.2, D3.3
D4-1: D4.1, E4.8
D4-2: D4.2, D4.4, P1.8
D4-5: D4.5, E4.9
D4-9: D4.9, D4.12, E5.8
D5-1: D5.1, D6.6
D5-2: D5.2, D6.8
D5-6: D5.6, F6.5, H6.11, J6.9
D5-8: D5.8, E5.9
D5-11: D5.11, D5.12, F4.13
D5-13: D5.13, D6.11
D6-2: D6.2, J8.13
D6-3: D6.3, J8.14
D6-4: D6.4, D7.6
D6-5: D6.5, E6.8
D6-9: D6.9, E6.3
D6-10: D6.10, D7.12
D6-12: D6.12, E6.11
D6-13: D6.13, D7.10
D7-1: D7.1, E7.13
D7-2: D7.2, E7.14
D7-4: D7.4, E7.4
D7-8: D7.8, E7.5
D8-1: D8.1, E8.11, E8.14
D8-2: D8.2, E8.9
D8-4: D8.4, E8.8
E1-3: E1.3, E2.6, F1.9
E1-5: E1.5, H5.9
E2-1: E2.1, F1.13, F4.9
E2-4: E2.4, E2.11, E4.5
E2-12: E2.12, E4.4
E2-13: E2.13, E3.11, E4.1, H1.9, P3.9
E3-9: E3.9, F3.14, H1.6, P3.5
E4-3: E4.3, F4.8
E5-3: E5.3, F7.1, F9.4
E5-4: E5.4, L2.2, L2.3, N2.2, N2.3
E5-6: E5.6, K8.1
E6-1: E6.1, E7.6
E6-10: E6.10, E7.3
E6-13: E6.13, E7.2
E7-11: E7.11, E7.12
E8-1: E8.1, E9.3
E8-2: E8.2, E8.3, F8.11
E8-12: E8.12, H8.13
F1-5: F1.5, H4.6
F1-10: F1.10, H5.2
F1-11: F1.11, F2.6
F1-12: F1.12, F2.8
F2-3: F2.3, F2.4
F2-10: F2.10, F2.11
F4-3: F4.3, F4.4
F4-5: F4.5, F4.11
F4-6: F4.6, F5.1, F5.2
F5-3: F5.3, H5.6
F5-4: F5.4, H5.5
F5-5: F5.5, H5.4
F5-6: F5.6, H5.3
F5-10: F5.10, H5.14
F5-11: F5.11, H5.13
F5-12: F5.12, H5.12
F5-13: F5.13, H5.11
F6-1: F6.1, J3.3, N4.6
F6-3: F6.3, F7.6
F6-4: F6.4, J6.4
F6-6: F6.6, H6.10
F6-9: F6.9, H6.9
F6-10: F6.10, J6.8
F6-11: F6.11, F7.11, F7.12
F7-2: F7.2, F7.3, K1.8
F7-4: F7.4, F8.4, H8.9
F8-1: F8.1, H8.12
F8-3: F8.3, H8.11
F8-5: F8.5, H8.8
F8-6: F8.6, F8.12
F9-1: F9.1, F9.2
F9-3: F9.3, H9.12, M7.14
F9-10: F9.10, H8.10
F9-11: F9.11, H9.11
F9-12: F9.12, F9.13
GND: A1.7, A2.7, A3.7, A4.7, A5.7, A6.7, A7.10, A8.2, A8.3, A8.10, B1.7, B2.2, B2.3, B2.10, B3.7, B4.8, B4.14, B5.8, B6.7, B7.7, B8.7, B9.7, C1.7, C2.2, C2.3, C2.10, C3.7, C4.8, C4.14, C5.8, C6.2, C6.3, C6.10, C7.8, C7.12, C8.7, C9.6, C9.7, C9.10, D1.7, D2.7, D3.7, D4.7, D5.7, D6.7, D7.7, D8.7, E2.7, E3.7, E4.2, E4.7, E5.7, E6.7, E7.8, E8.10, E9.1, F1.7, F2.7, F3.2, F3.3, F3.10, F4.7, F5.7, F6.7, F7.8, F8.7, F9.7, H1.7, H2.7, H3.2, H3.3, H3.10, H4.7, H5.8, H5.10, H5.15, H6.7, H6.12, H7.7, H8.7, H9.7, J1.7, J3.7, J4.2, J4.3, J4.10, J5.7, J6.7, J7.5, J7.6, J7.8, J8.8, J9.7, K1.7, K3.2, K3.3, K3.10, K4.2, K4.3, K4.10, K5.7, K6.7, K7.3, K7.4, K7.5, K7.6, K7.8, K8.7, K9.7, L1.2, L1.4, L1.5, L1.7, L1.8, L2.10, L3.7, L4.7, L5.7, L6.7, L7.7, L8.7, L9.7, M1.8, M2.8, M2.15, M3.2, M3.3, M3.10, M4.2, M4.3, M4.10, M5.7, M6.7, M7.2, M7.3, M7.10, M8.7, M9.8, M9.12, N1.2, N1.3, N1.5, N1.6, N1.7, N1.8, N2.6, N2.7, N2.10, N3.7, N4.7, N5.7, N6.7, N7.2, N7.3, N7.10, N8.4, N8.7, N9.2, N9.3, N9.10, P1.7, P3.8, P4.7
H1-8: H1.8, J1.4, J1.10
H6-2: H6.2, M4.12
H7-1: H7.1, K9.4, K9.12
H7-4: H7.4, J7.4
H7-5: H7.5, J6.2, J7.3
H7-6: H7.6, K8.3
H7-8: H7.8, H7.11, M7.12
H7-9: H7.9, H9.9
H7-10: H7.10, H8.3
H7-12: H7.12, H9.8
H7-13: H7.13, H8.1
H8-2: H8.2, J8.4
H8-4: H8.4, J8.5
H8-5: H8.5, J8.7
H8-6: H8.6, K8.2, K8.5, K8.9, K8.12
H9-2: H9.2, K9.3
J1-8: J1.8, J1.12
J3-1: J3.1, N4.3
J3-2: J3.2, N4.4
J4-1: J4.1, J4.12
J5-3: J5.3, K5.2
J5-8: J5.8, K5.4, N5.2
J5-11: J5.11, N5.13
J6-1: J6.1, L7.8
J6-5: J6.5, K1.5, N5.12
J6-11: J6.11, J7.13
J6-13: J6.13, J7.12
J7-9: J7.9, K6.11, K7.9
J7-15: J7.15, K7.7, K7.10
J8-2: J8.2, K8.13
J8-3: J8.3, K8.10
J8-6: J8.6, K8.4
J8-11: J8.11, J8.12
J9-3: J9.3, J9.10
J9-11: J9.11, K9.8
J9-13: J9.13, K9.10, K9.11
K1-1: K1.1, N1.14
K1-2: K1.2, L1.14
K1-4: K1.4, K5.6
K3-1: K3.1, K3.12
K3-9: K3.9, M5.5
K3-11: K3.11, K4.1, L4.13
K3-14: K3.14, L3.8
K4-8: K4.8, L4.9
K4-9: K4.9, L4.10
K6-2: K6.2, L7.3, L7.12
K6-3: K6.3, L7.11
K6-6: K6.6, L7.10
K6-10: K6.10, L6.3, L6.8, L6.11
K6-12: K6.12, L6.2
K6-13: K6.13, K7.11
K8-6: K8.6, L8.2
K8-8: K8.8, L8.9
K8-11: K8.11, L8.12
K9-1: K9.1, N8.1, N8.5
K9-2: K9.2, N8.3
K9-5: K9.5, N3.8
K9-6: K9.6, K9.9
L1-1: L1.1, M1.15
L1-3: L1.3, M1.9
L1-6: L1.6, M1.12
L1-9: L1.9, M1.11
L2-1: L2.1, L2.12, M2.3
L2-8: L2.8, M2.13
L2-9: L2.9, M2.6
L2-11: L2.11, M2.10
L2-14: L2.14, M2.11, N2.11
L3-3: L3.3, L3.4, L5.11
L3-6: L3.6, M3.14
L3-10: L3.10, L3.11
L3-13: L3.13, L5.10
L4-1: L4.1, M3.11, M4.1
L4-2: L4.2, M4.11
L4-4: L4.4, M4.9
L4-5: L4.5, M4.8
L4-6: L4.6, L5.3
L4-8: L4.8, L5.9
L5-4: L5.4, M4.14, N6.10
L5-5: L5.5, M3.9
L5-6: L5.6, M5.9
L5-8: L5.8, N6.4
L7-1: L7.1, L8.3
L7-2: L7.2, L8.8
L7-6: L7.6, L7.9
L7-13: L7.13, L8.11
L8-1: L8.1, L9.6
L8-6: L8.6, M7.1
L8-10: L8.10, L9.8
L8-13: L8.13, L9.10
L9-5: L9.5, M9.1, M9.2, M9.4, M9.6, M9.9
L9-9: L9.9, M9.5
L9-11: L9.11, M9.3, M9.7
M1-1: M1.1, M2.7
M1-2: M1.2, M2.12
M1-6: M1.6, M2.9
M1-7: M1.7, M2.4
M1-10: M1.10, N1.9
M1-13: M1.13, N1.1
M1-14: M1.14, N1.4
M2-2: M2.2, N2.1, N2.12
M2-5: M2.5, N2.9
M2-14: M2.14, N2.8
M3-1: M3.1, M3.12
M5-1: M5.1, M5.13, M6.11, N5.3, N5.11
M5-2: M5.2, M5.12, M6.3
M5-4: M5.4, N5.5, N6.6
M5-6: M5.6, N4.1
M5-8: M5.8, N4.12
M5-10: M5.10, N5.9, N6.8
M6-8: M6.8, N5.4, N5.10
M9-13: M9.13, N9.11
M9-14: M9.14, N9.8
M9-15: M9.15, N9.9
N3-4: N3.4, P3.13
N4-2: N4.2, N5.6
N4-5: N4.5, N4.8
N4-10: N4.10, N4.11
N4-13: N4.13, N5.8
N8-2: N8.2, N8.11
P3-7: P3.7, P4.1
VCC: A7.3, B5.1, B5.9, B5.10, B5.15, C1.1, C1.10, C1.13, C5.1, C5.9, C5.10, C5.15, C8.1, C8.4, E4.10, E4.13, E7.1, E7.9, E7.10, E7.15, F5.9, F8.2, H6.1, H6.4, H9.1, H9.10, H9.13, J1.1, J1.13, J7.1, J7.7, J7.10, J8.1, J8.9, J8.10, J8.15, K7.1, L6.1, L6.10, L6.13, M1.3, M1.4, M1.5, M8.8, M8.11, N7.14, N8.8
_1H: C2.1, C2.12, D2.13, J7.2, K7.2, L8.4, P3.14
_1V: A4.2, A5.13, E3.1, F2.1, F3.1, F3.12, H1.12
_1V_n: E3.2, F1.3
_2F: H6.3, J4.9
_2H: C2.9, D2.9, D3.1
_2H_n: D1.9, D2.8
_2V: D5.9, E3.3, F2.12, F3.9, F4.12, H1.13, L3.2, L7.4, N1.11
_2V_n: A6.11, E3.4, F4.2
_2XV: E3.10, F7.15
_4H: C2.8, C3.2, L1.11, P4.9
_4HR: M7.8, P4.13
_4HR_n: M6.2, P4.12
_4H_n: P1.10, P4.8
_4M_n: J5.1, J6.10
_4V: D8.10, E2.2, E2.3, E3.5, F2.2, F2.13, F3.8, H4.11, K5.5, N1.12
_4V_n: E2.10, E3.6, F4.10, H1.10, P3.10
_8F: D8.5, D8.9, J4.11
_8H: B2.14, C2.11, C3.9, L1.13, P4.11
_8HR: L5.1, M7.11, N7.1
_8HR_n: L5.2, M6.9
_8H_n: P1.11, P4.10
_8M_n: J5.13, J6.12
_8V: F3.11, H3.14, H4.9, L1.12, N1.13
_16H: A2.1, B1.13, B2.1, B2.12, C3.12
_16HR: M6.10, M6.12, N7.9
_16H_n: A2.2, D1.5
_16M: J5.10, J5.12, J7.11
_16V: A4.12, H2.11, H3.1, H3.12, H4.10, J3.13
_16V_n: A6.13, F7.14, J3.12
_32H: A2.5, B2.9, B3.5
_32HR: M6.1, M6.13, N7.8
_32H_n: A1.1, A2.6, M2.1
_32M: J5.2, J5.9, K7.14
_32V: H2.12, H3.9, H4.4, J3.5
_32V_n: A5.11, J3.6
_64H: A2.9, B2.8, B3.2, D1.6
_64HR: L5.13, M8.9, N3.3, N6.5, N7.11, P3.15
_64HR_n: L5.12, N6.9
_64H_n: A1.2, A1.13, A2.8, B1.1, H1.1
_64M: K5.13, K7.13
_64V: A5.10, H3.8, H4.5, J3.9
_64V_n: H2.4, J3.8
_128H: A2.3, B2.11, B3.9, C1.9, C1.12, H1.4, H1.5, H2.6, P3.6
_128H_n: A2.4, B1.12
_128M: K5.9, K5.10, K7.12, L6.9, L6.12
_128V: H3.11, H4.3, J3.11, J4.14
_128V_n: A5.9, D5.5, H2.3, J3.10
_A0: A2.12, A3.11, B1.9, H1.2
_A0_n: A1.6, A2.13, C1.4
_A1: A6.1, B3.12, C1.2, H2.5
_A1_n: A1.5, A5.2, C1.3, C1.8, C1.11, D1.11
_A2: C1.6, L3.12
_A2M: K5.12, L6.6
_A2M_n: K6.9, L6.5
_AFT: D1.12, D2.4
_AOM_n: K6.8, L6.4
_CAR_BODY: F6.2, F6.12, J6.6
_CR1: A3.2, A3.4, A3.6, A3.8, A3.10, D2.11, D3.6, D3.8, D3.10, D3.12
_CRASH: B9.9, F7.7, K6.4
_DIVIDER_n: N3.6, N3.9
_DOTS: K4.12, L3.5, L3.9, N3.5
_FLASH: D8.6, H2.2
_Fx: A8.14, B8.9, C6.12
_Fy: A8.9, B8.1
_GO: D5.4, D8.13, H9.6
_GT: D6.1, E9.4, F8.13, F9.6, F9.9
_GT_n: A7.2, B9.11, F9.5, F9.8
_HBLANK: H7.2, P4.2
_HSYNC: E3.8, J9.5
_LorR: B8.12, D4.13, E5.1, E7.7, F4.1
_LorR_n: B6.13, D4.10, E5.2, E6.2, E6.9, E6.12
_MCW: A4.11, B7.9, E5.5, H5.1
_OFR: B9.5, D8.12, F7.9
_RFD: C8.12, C9.12
_RFX: C8.2, C9.14, N9.12
_ROAD: L8.5, M8.6, N3.10
_ROAD_n: F6.13, M8.5
_SCORE_AND_ME_VIDEO: K1.6, K9.13
_SP_n: A4.5, A5.1, C6.1, C6.14, F1.2, F6.8, J1.3
_SR: F1.1, F5.8, L7.5
_TRAFFIC_n: J3.4, N3.11
_VBLANK: F7.13, H7.3
_VSYNC: E3.13, F1.4, H9.3, J9.9, K6.5, L3.1
_VSYNC_n: B4.11, C4.11, E3.12, N8.10, N8.13, P3.11, P3.12
_XPP: D2.2, D5.3
